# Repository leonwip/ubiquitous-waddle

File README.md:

# ubiquitous-waddle

This is an open-source dual channel CAN FD to USB-C adapter. It is meant to be
used with the Zephyr-based [CANnectivity][1] firmware.

## Firmware

### Building

Assuming you already have a working Zephyr development environment (see
[Getting Started Guide][2]), the firmware workspace can be initialized using:
```sh
west init -m "https://github.com/leonwip/ubiquitous-waddle" --mr main my-workspace
cd my-workspace
west update
```

Then to build the release variant (with reduced logging):
```sh
west build -b ubiquitous_waddle --sysbuild cannectivity/app -- -DSB_CONF_FILE=sysbuild-dfu.conf -DFILE_SUFFIX=usbd_next_release
```

### Flashing

To flash via JLink (SWD):
```sh
west flash --runner jlink
```

To flash via USB DFU:
```
dfu-util -a 0 -D build/app/zephyr/zephyr.signed.bin.dfu
```

## Example Usage

Verify successful connection:
```sh
$ lsusb | grep CANnectivity
Bus 005 Device 014: ID 1209:ca01 Generic CANnectivity USB to CAN adapter
```

Determine interface names:
```sh
$ ip link show type can
16: can0: <NOARP,ECHO> mtu 16 qdisc noop state DOWN mode DEFAULT group default qlen 10
    link/can
17: can1: <NOARP,ECHO> mtu 16 qdisc noop state DOWN mode DEFAULT group default qlen 10
    link/can
```

Bring up the interface (with FD on):
```sh
sudo ip link set can0 up type can bitrate 250000 dbitrate 1000000 fd on
```

Send some frames (`##1` opposed to just `#` turns on BRS):
```sh
cansend can0 123#11.22.33
cansend can0 123##111.22.33
```

## License

CANnectivity is licensed under the [Apache-2.0][3] license. This board is
licensed under the [CERN-OHL-P-2.0](./LICENSE) license.

[1]: https://github.com/CANnectivity/cannectivity
[2]: https://docs.zephyrproject.org/latest/develop/getting_started/index.html
[3]: https://github.com/CANnectivity/cannectivity/blob/main/LICENSE

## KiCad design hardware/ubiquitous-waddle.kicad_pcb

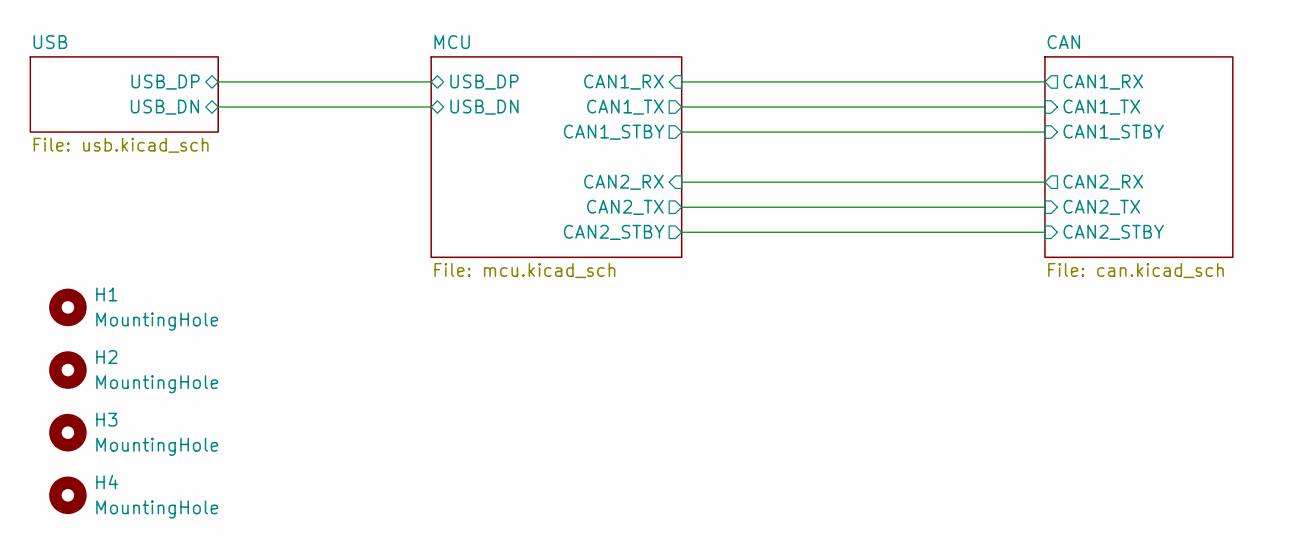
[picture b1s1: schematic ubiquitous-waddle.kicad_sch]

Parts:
H1, H2, H3, H4: MountingHole; MountingHole_2.7mm_M2.5

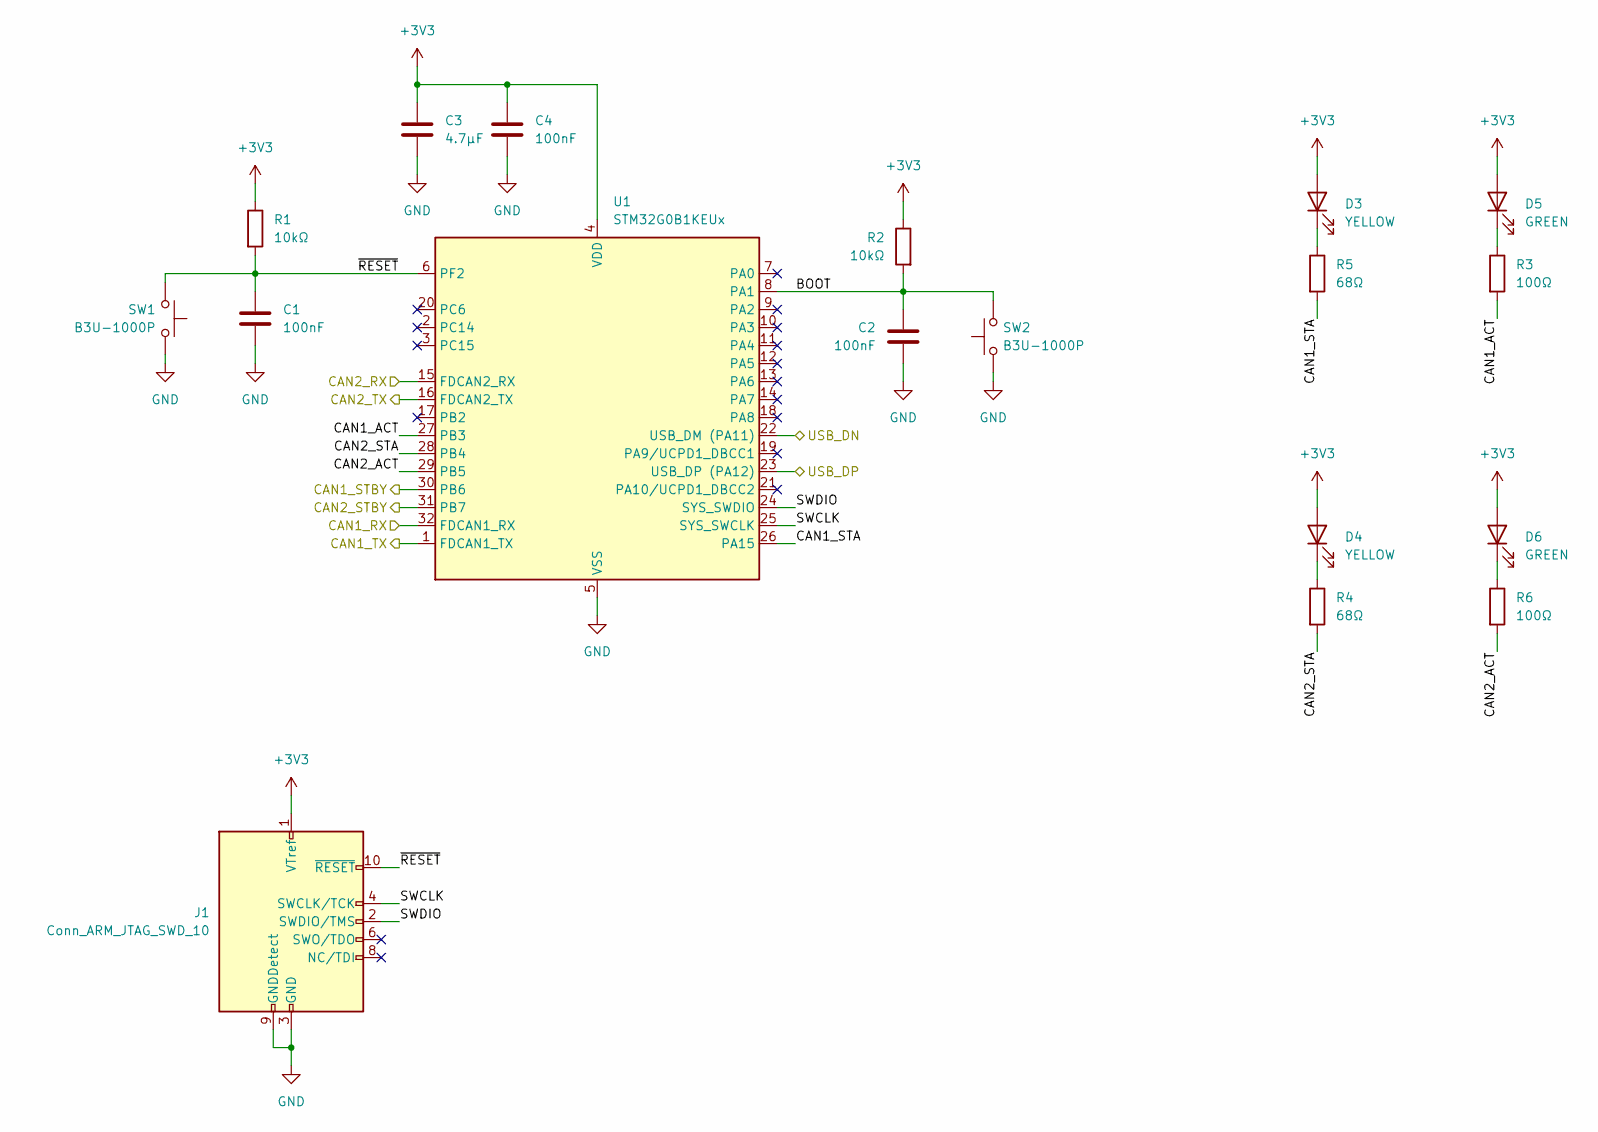
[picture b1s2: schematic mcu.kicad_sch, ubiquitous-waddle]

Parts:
C1, C2, C4: 100nF; C_0402_1005Metric; Mouser No 81-GRM155R71A104KA1D
C3: 4.7µF; C_0402_1005Metric; Mouser No 81-GRM155R61A475MEAD
D3, D4: YELLOW; LED_0603_1608Metric; Mouser No 710-150060YS55040
D5, D6: GREEN; LED_0603_1608Metric; Mouser No 710-150060GS55040
J1: Conn_ARM_JTAG_SWD_10; PinHeader_2x05_P1.27mm_Vertical_SMD; Mouser No 200-FTSH10501FDVK
R1, R2: 10kΩ; R_0402_1005Metric; Mouser No 603-RC0402FR-0710KL
R3, R6: 100Ω; R_0402_1005Metric; Mouser No 603-RC0402FR-07100RL
R4, R5: 68Ω; R_0402_1005Metric; Mouser No 603-RC0402FR-0768RL
SW1, SW2: B3U-1000P; SW_SPST_B3U-1000P; Mouser No 653-B3U-1000P
U1: STM32G0B1KEUx; QFN-32-1EP_5x5mm_P0.5mm_EP3.45x3.45mm_ThermalVias; Mouser No 511-STM32G0B1KEU6

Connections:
+3V3: C3.1, C4.1, D3.2 (A), D4.2 (A), D5.2 (A), D6.2 (A), J1.1 (VTref), R1.1, R2.1, U1.4 (VDD); also elsewhere on the board
/CAN/CAN1_RX: U1.32 (FDCAN1_RX); also elsewhere on the board
/CAN/CAN1_STBY: U1.30 (PB6); also elsewhere on the board
/CAN/CAN1_TX: U1.1 (FDCAN1_TX); also elsewhere on the board
/CAN/CAN2_RX: U1.15 (FDCAN2_RX); also elsewhere on the board
/CAN/CAN2_STBY: U1.31 (PB7); also elsewhere on the board
/CAN/CAN2_TX: U1.16 (FDCAN2_TX); also elsewhere on the board
/MCU/BOOT: C2.1, R2.2, SW2.2, U1.8 (PA1)
/MCU/CAN1_ACT: R3.2, U1.27 (PB3)
/MCU/CAN1_STA: R5.2, U1.26 (PA15)
/MCU/CAN2_ACT: R6.2, U1.29 (PB5)
/MCU/CAN2_STA: R4.2, U1.28 (PB4)
/MCU/SWCLK: J1.4 (SWCLK/TCK), U1.25 (SYS_SWCLK)
/MCU/SWDIO: J1.2 (SWDIO/TMS), U1.24 (SYS_SWDIO)
/MCU/USB_DN: U1.22 (USB_DM (PA11)); also elsewhere on the board
/MCU/USB_DP: U1.23 (USB_DP (PA12)); also elsewhere on the board
/MCU/~RESET: C1.1, J1.10 (~RESET), R1.2, SW1.2, U1.6 (PF2)
GND: C1.2, C2.2, C3.2, C4.2, J1.3 (GND), J1.5 (GND), J1.9 (GNDDetect), SW1.1, SW2.1, U1.5 (VSS), U1.33 (VSS); also elsewhere on the board
unnamed: D3.1 (K), R5.1
unnamed: D4.1 (K), R4.1
unnamed: D5.1 (K), R3.1
unnamed: D6.1 (K), R6.1

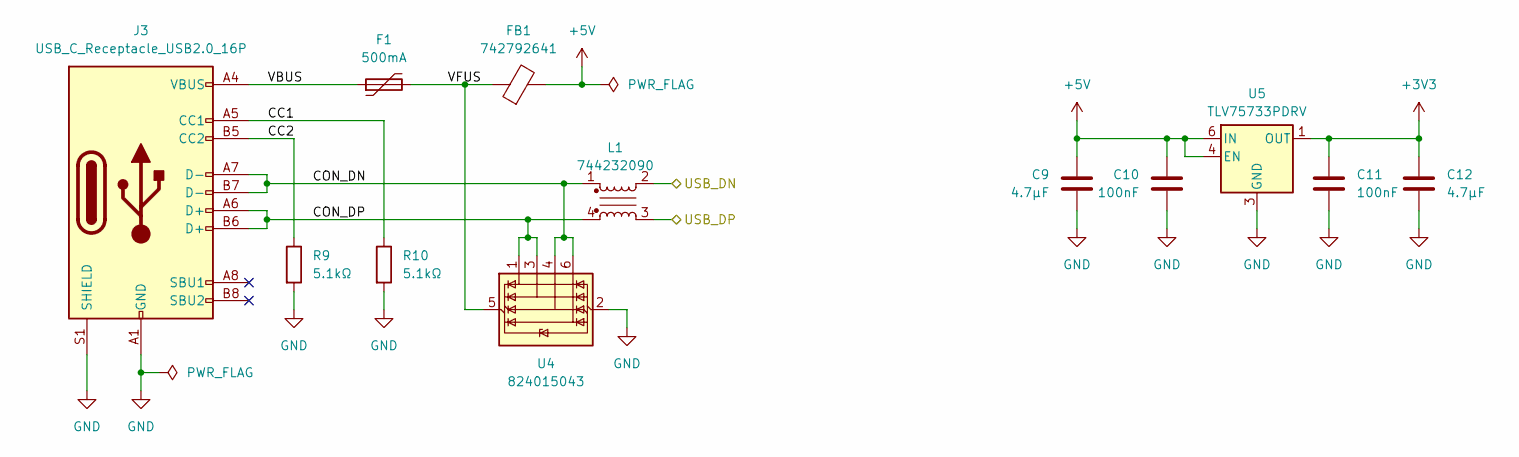
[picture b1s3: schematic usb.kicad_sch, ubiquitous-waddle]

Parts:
C9, C12: 4.7µF; C_0402_1005Metric; Mouser No 81-GRM155R61A475MEAD
C10, C11: 100nF; C_0402_1005Metric; Mouser No 81-GRM155R71A104KA1D
F1: 500mA; Fuse_0603_1608Metric; Mouser No 652-MF-FSML050/8-2
FB1: 742792641; L_0603_1608Metric; Mouser No 710-742792641
J3: USB_C_Receptacle_USB2.0_16P; USB_C_Receptacle_GCT_USB4105-xx-A_16P_TopMnt_Horizontal; Mouser No 640-USB4105-GF-A-060
L1: 744232090; L_CommonMode_Wurth_WE-CNSW-1206; Mouser No 710-744232090
R9, R10: 5.1kΩ; R_0402_1005Metric; Mouser No 71-CRCW0402-5.1K-E3
U4: 824015043; SOT-23-6; Mouser No 710-824015043
U5: TLV75733PDRV; WSON-6-1EP_2x2mm_P0.65mm_EP1x1.6mm; Mouser No 595-TLV75733PDRVR

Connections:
+3V3: C11.1, C12.1, U5.1 (OUT); also elsewhere on the board
+5V: C9.1, C10.1, FB1.2, U5.4 (EN), U5.6 (IN); also elsewhere on the board
/MCU/USB_DN: L1.2; also elsewhere on the board
/MCU/USB_DP: L1.3; also elsewhere on the board
/USB/CC1: J3.A5 (CC1), R10.1
/USB/CC2: J3.B5 (CC2), R9.1
/USB/CON_DN: J3.A7 (D-), J3.B7 (D-), L1.1, U4.4 (I/O3), U4.6 (I/O4)
/USB/CON_DP: J3.A6 (D+), J3.B6 (D+), L1.4, U4.1 (I/O1), U4.3 (I/O2)
/USB/VBUS: F1.1, J3.A4 (VBUS), J3.A9 (VBUS), J3.B4 (VBUS), J3.B9 (VBUS)
/USB/VFUS: F1.2, FB1.1, U4.5 (VBUS)
GND: C9.2, C10.2, C11.2, C12.2, J3.A1 (GND), J3.A12 (GND), J3.B1 (GND), J3.B12 (GND), J3.S1 (SHIELD), R9.2, R10.2, U4.2 (GND), U5.3 (GND), U5.7 (GND); also elsewhere on the board

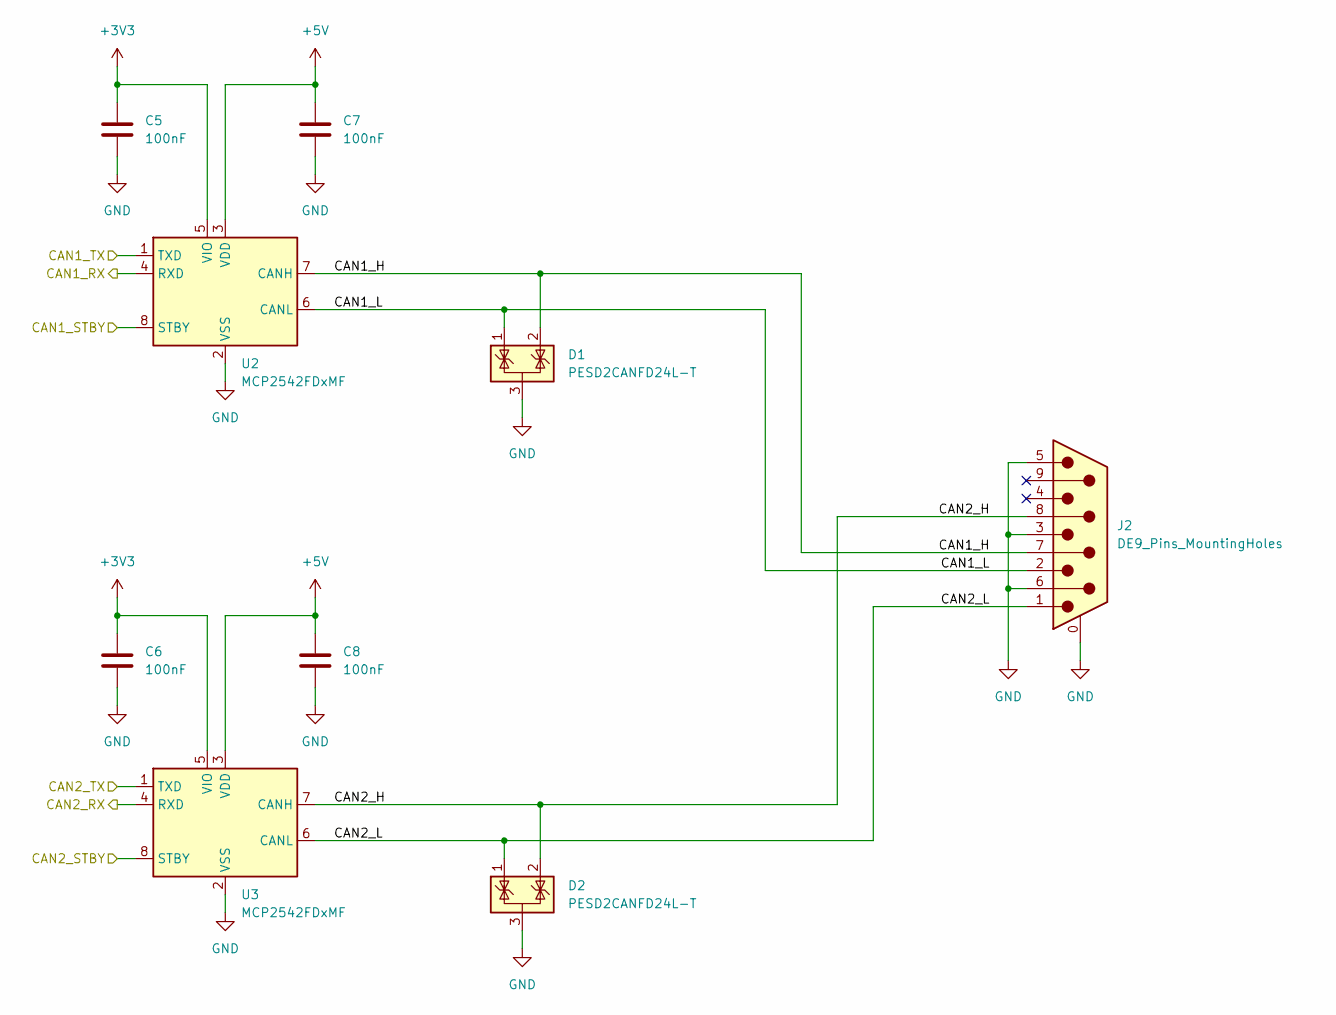
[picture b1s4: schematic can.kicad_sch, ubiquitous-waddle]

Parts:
C5, C6, C7, C8: 100nF; C_0402_1005Metric; Mouser No 81-GRM155R71A104KA1D
D1, D2: PESD2CANFD24L-T; SOT-23; Mouser No 771-PESD2CANFD24L-TR
J2: DE9_Pins_MountingHoles; DSUB-9_Pins_Horizontal_P2.77x2.84mm_EdgePinOffset9.90mm_Hou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; Mouser No 649-D09P13A4GV00LF
U2, U3: MCP2542FDxMF; DFN-8-1EP_3x3mm_P0.65mm_EP1.55x2.4mm; Mouser No 579-MCP2542FDT-E/MF

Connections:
+3V3: C5.1, C6.1, U2.5 (VIO), U3.5 (VIO); also elsewhere on the board
+5V: C7.1, C8.1, U2.3 (VDD), U3.3 (VDD); also elsewhere on the board
/CAN/CAN1_H: D1.2 (K), J2.7, U2.7 (CANH)
/CAN/CAN1_L: D1.1 (K), J2.2, U2.6 (CANL)
/CAN/CAN1_RX: U2.4 (RXD); also elsewhere on the board
/CAN/CAN1_STBY: U2.8 (STBY); also elsewhere on the board
/CAN/CAN1_TX: U2.1 (TXD); also elsewhere on the board
/CAN/CAN2_H: D2.2 (K), J2.8, U3.7 (CANH)
/CAN/CAN2_L: D2.1 (K), J2.1, U3.6 (CANL)
/CAN/CAN2_RX: U3.4 (RXD); also elsewhere on the board
/CAN/CAN2_STBY: U3.8 (STBY); also elsewhere on the board
/CAN/CAN2_TX: U3.1 (TXD); also elsewhere on the board
GND: C5.2, C6.2, C7.2, C8.2, D1.3 (A), D2.3 (A), J2.0 (PAD), J2.3, J2.5, J2.6, U2.2 (VSS), U2.9 (VSS), U3.2 (VSS), U3.9 (VSS); also elsewhere on the board

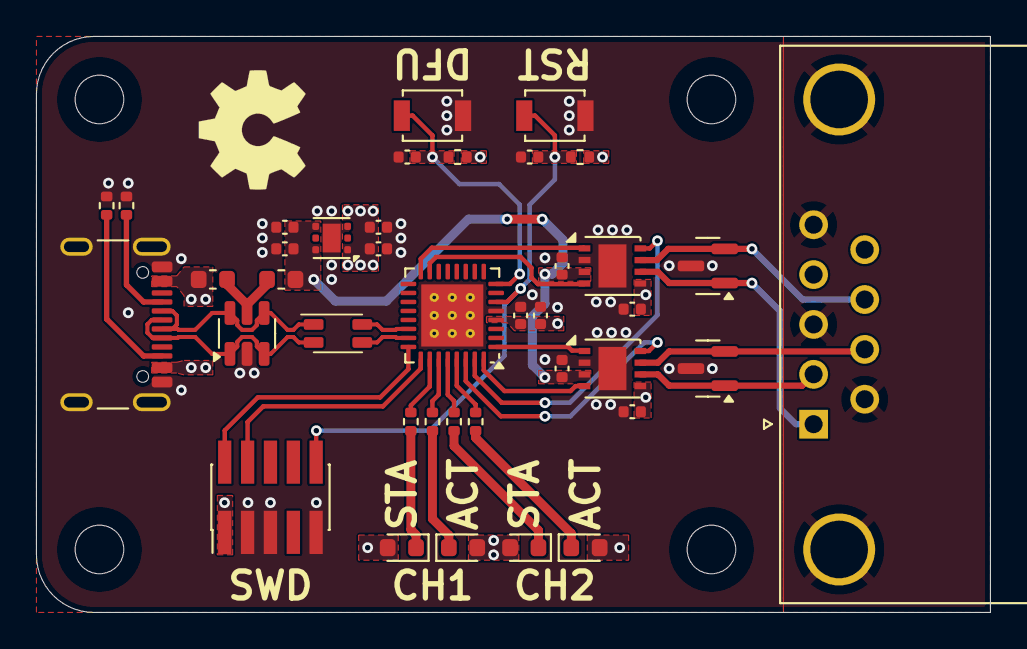
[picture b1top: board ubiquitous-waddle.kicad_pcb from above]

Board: 4 copper layers, 53.0 x 32.0 mm, 43 parts (0 on the bottom side), 33 nets.

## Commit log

2025-10-12 fix: little typo in `README.md`
2025-10-12 fix: remove obsolete sheet
2025-12-22 add hardware revision v2
2025-12-22 feat: add nix dev shell
2026-01-02 feat!: use `device_next`, bump dependencies
    Switch to the experimental `device_next` USB device stack.
    Bump Zephyr and CANnectivity to v4.3.0 and v1.3.0 respectively.
